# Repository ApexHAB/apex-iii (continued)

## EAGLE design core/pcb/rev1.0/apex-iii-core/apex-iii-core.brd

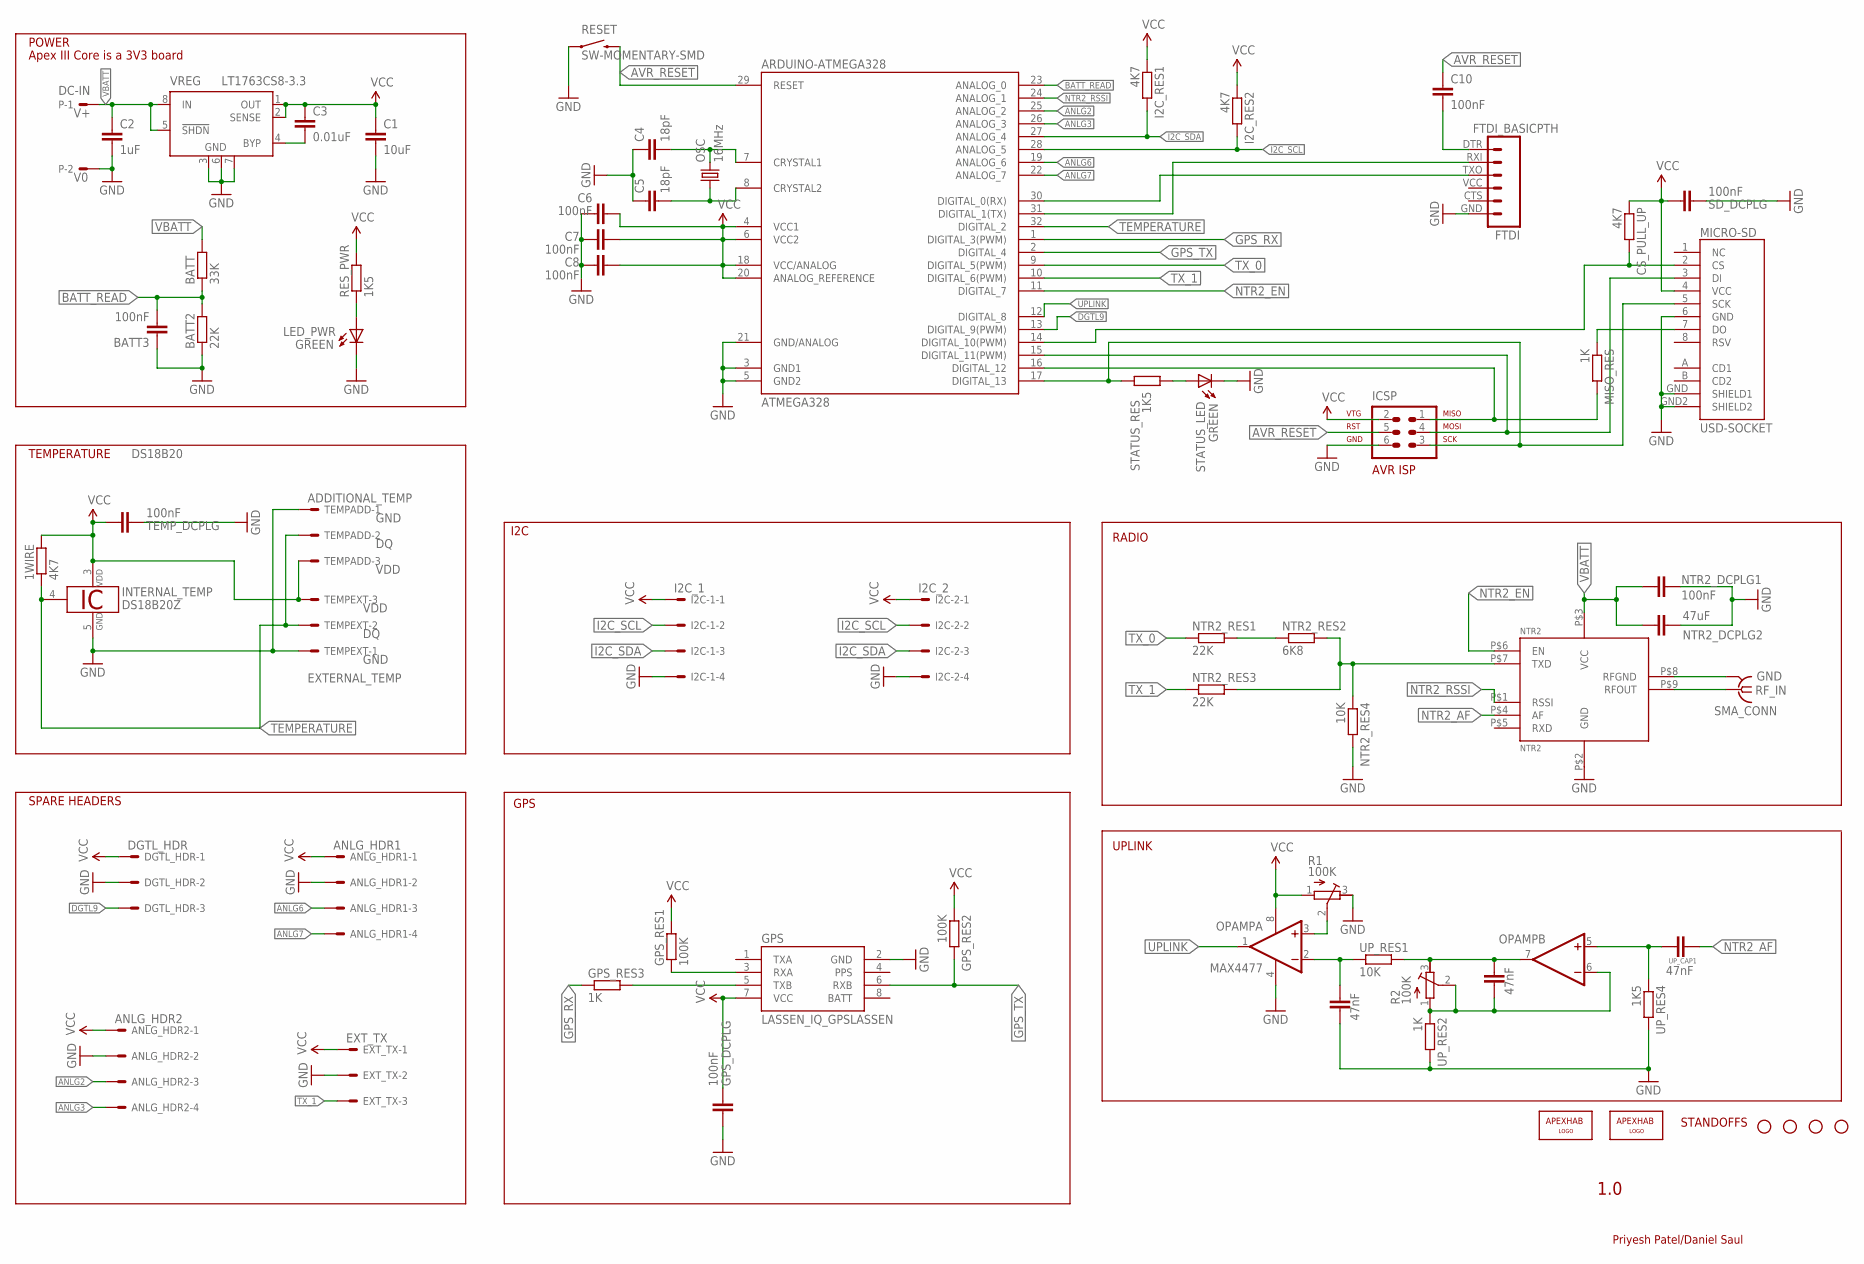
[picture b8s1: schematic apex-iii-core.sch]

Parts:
1WIRE: 4K7; R0805
ANLG_HDR1: ANLG_HDR1; 6410-04
ANLG_HDR2: ANLG_HDR2; 6410-04
ARDUINO-ATMEGA328: ATMEGA328; TQFP32-08
BATT: 33K; R0805
BATT2: 22K; R0805
BATT3: 100nF; 0805
C1: 10uF; 0805
C2: 1uF; 0805
C3: 0.01uF; 0805
C4, C5: 18pF; 0805
C6, C7, C8, C10: 100nF; 0805
CS_PULL_UP: 4K7; R0805
DGTL_HDR: DGTL_HDR; 6410-03
EXT_TX: EXT_TX; 6410-03
FTDI: FTDI_BASICPTH; FTDI_BASIC
GPS: LASSEN_IQ_GPSLASSEN; LASSEN_IQ_GPS
GPS_DCPLG: 100nF; 0805
GPS_RES1, GPS_RES2: 100K; R0805
GPS_RES3: 1K; R0805
I2C-1: I2C_1; 6410-04
I2C-2: I2C_2; 6410-04
I2C_RES1, I2C_RES2: 4K7; R0805
ICSP: AVR-ISP-6
INTERNAL_TEMP: DS18B20Z; SO08
JP1, JP2, JP3, JP4: STAND-OFF
JP5: APEXHAB-LOGO_APEXHAB-SMALL; APEXHAB-LOGO-SMALL
JP6: APEXHAB-LOGO_APEXHAB; APEXHAB-LOGO
LED_PWR: GREEN; CHIPLED_0603
MICRO-SD: USD-SOCKET; MICRO-SD-PUSH-PULL
MISO_RES: 1K; R0805
NTR2: NTR2
NTR2_DCPLG1: 100nF; 0805
NTR2_DCPLG2: 47uF; 0805
NTR2_RES1, NTR2_RES3: 22K; R0805
NTR2_RES2: 6K8; R0805
NTR2_RES4: 10K; R0805
OPAMP: MAX4477; SO08
OSC: 16MHz; CRYSTAL-SMD-5X3
P: DC-IN; 6410-02
R1, R2: 100K; RTRIM3214W
RESET: SW-MOMENTARY-SMD; TACTILE-SWITCH-1101NE
RES_PWR: 1K5; R0805
SD_DCPLG: 100nF; 0805
SMA_CONN: SMA-142-0701-801/806; J502-ND-142-0701-801/806
STATUS_LED: GREEN; CHIPLED_0603
STATUS_RES: 1K5; R0805
TEMPADD: ADDITIONAL_TEMP; 6410-03
TEMPEXT: EXTERNAL_TEMP; 6410-03
TEMP_DCPLG: 100nF; 0805
UP_CAP1, UP_CAP3, UP_CAP4: 47nF; 0805
UP_RES1: 10K; R0805
UP_RES2: 1K; R0805
UP_RES4: 1K5; R0805
VREG: LT1763CS8-3.3; SOIC8

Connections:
ANLG2: ANLG_HDR2.3, ARDUINO-ATMEGA328.25 (ANALOG_2)
ANLG3: ANLG_HDR2.4, ARDUINO-ATMEGA328.26 (ANALOG_3)
ANLG6: ANLG_HDR1.3, ARDUINO-ATMEGA328.19 (ANALOG_6)
ANLG7: ANLG_HDR1.4, ARDUINO-ATMEGA328.22 (ANALOG_7)
AVR_RESET: ARDUINO-ATMEGA328.29 (RESET), C10.1, ICSP.5, RESET.P$2 (2)
BATT: GPS.8 (BATT)
BATT_READ: ARDUINO-ATMEGA328.23 (ANALOG_0), BATT.1, BATT2.2, BATT3.2
DGTL9: ARDUINO-ATMEGA328.13 (DIGITAL_9(PWM)), DGTL_HDR.3
GND: ANLG_HDR1.2, ANLG_HDR2.2, ARDUINO-ATMEGA328.3 (GND1), ARDUINO-ATMEGA328.5 (GND2), ARDUINO-ATMEGA328.21 (GND/ANALOG), BATT2.1, BATT3.1, C1.2, C2.2, C4.1, C5.1, C6.1, C7.1, C8.1, DGTL_HDR.2, EXT_TX.2, FTDI.GND (6), GPS.2 (GND), GPS_DCPLG.2, I2C-1.4, I2C-2.4, ICSP.6, INTERNAL_TEMP.5 (GND), LED_PWR.C, MICRO-SD.6 (GND), MICRO-SD.GND (SHIELD1), MICRO-SD.GND2 (SHIELD2), NTR2.P$2 (GND), NTR2.P$8 (RFGND), NTR2_DCPLG1.1, NTR2_DCPLG2.1, NTR2_RES4.2, OPAMP.4 (V-), P.2, R1.3 (A), RESET.P$1 (1), SD_DCPLG.1, SMA_CONN.G@1 (GND), SMA_CONN.G@2 (GND), SMA_CONN.G@3 (GND), SMA_CONN.G@4 (GND), STATUS_LED.C, TEMPADD.1, TEMPEXT.1, TEMP_DCPLG.1, UP_CAP4.2, UP_RES2.2, UP_RES4.2, VREG.3 (GND), VREG.6 (GND), VREG.7 (GND)
GPS_RX: ARDUINO-ATMEGA328.1 (DIGITAL_3(PWM)), GPS_RES3.1
GPS_TX: ARDUINO-ATMEGA328.2 (DIGITAL_4), GPS.6 (RXB), GPS_RES2.2
I2C_SCL: ARDUINO-ATMEGA328.28 (ANALOG_5), I2C-1.2, I2C-2.2, I2C_RES2.2
I2C_SDA: ARDUINO-ATMEGA328.27 (ANALOG_4), I2C-1.3, I2C-2.3, I2C_RES1.2
MISO: ARDUINO-ATMEGA328.16 (DIGITAL_12), ICSP.1, MISO_RES.2
MOSI: ARDUINO-ATMEGA328.15 (DIGITAL_11(PWM)), ICSP.4, MICRO-SD.3 (DI)
unnamed: C3.2, VREG.4 (BYP)
unnamed: MICRO-SD.7 (DO), MISO_RES.1
unnamed: LED_PWR.A, RES_PWR.1
unnamed: C10.2, FTDI.DTR (1)
unnamed: ARDUINO-ATMEGA328.8 (CRYSTAL2), C5.2, OSC.1
unnamed: ARDUINO-ATMEGA328.7 (CRYSTAL1), C4.2, OSC.3 (2)
unnamed: STATUS_LED.A, STATUS_RES.2
unnamed: ARDUINO-ATMEGA328.31 (DIGITAL_1(TX)), FTDI.RXI (2)
unnamed: ARDUINO-ATMEGA328.30 (DIGITAL_0(RX)), FTDI.TXO (3)
unnamed: ARDUINO-ATMEGA328.14 (DIGITAL_10(PWM)), CS_PULL_UP.2, MICRO-SD.2 (CS)
unnamed: NTR2.P$7 (TXD), NTR2_RES2.2, NTR2_RES3.2, NTR2_RES4.1
unnamed: GPS.3 (RXA), GPS_RES1.1
unnamed: GPS.5 (TXB), GPS_RES3.2
unnamed: OPAMP.3 (+IN), R1.2 (S)
unnamed: NTR2_RES1.2, NTR2_RES2.1
unnamed: OPAMP.5 (+IN), UP_CAP1.2, UP_RES4.1
unnamed: OPAMP.7 (OUT), R2.3 (A), UP_CAP3.1, UP_RES1.2
unnamed: OPAMP.6 (-IN), R2.1 (E), R2.2 (S), UP_CAP3.2, UP_RES2.1
NTR2_AF: NTR2.P$4 (AF), UP_CAP1.1
NTR2_EN: ARDUINO-ATMEGA328.11 (DIGITAL_7), NTR2.P$6 (EN)
NTR2_RSSI: ARDUINO-ATMEGA328.24 (ANALOG_1), NTR2.P$1 (RSSI)
RANDOM: OPAMP.2 (-IN), UP_CAP4.1, UP_RES1.1
RF_IN: NTR2.P$9 (RFOUT), SMA_CONN.1
SCK: ARDUINO-ATMEGA328.17 (DIGITAL_13), ICSP.3, MICRO-SD.5 (SCK), STATUS_RES.1
TEMPERATURE: 1WIRE.1, ARDUINO-ATMEGA328.32 (DIGITAL_2), INTERNAL_TEMP.4 (1W), TEMPADD.2, TEMPEXT.2
TX_0: ARDUINO-ATMEGA328.9 (DIGITAL_5(PWM)), NTR2_RES1.1
TX_1: ARDUINO-ATMEGA328.10 (DIGITAL_6(PWM)), EXT_TX.3, NTR2_RES3.1
UPLINK: ARDUINO-ATMEGA328.12 (DIGITAL_8), OPAMP.1 (OUT)
VBATT: BATT.2, C2.1, NTR2.P$3 (VCC), NTR2_DCPLG1.2, NTR2_DCPLG2.2, P.1, VREG.5 (!SHDN), VREG.8 (IN)
VCC: 1WIRE.2, ANLG_HDR1.1, ANLG_HDR2.1, ARDUINO-ATMEGA328.4 (VCC1), ARDUINO-ATMEGA328.6 (VCC2), ARDUINO-ATMEGA328.18 (VCC/ANALOG), ARDUINO-ATMEGA328.20 (ANALOG_REFERENCE), C1.1, C3.1, C6.2, C7.2, C8.2, CS_PULL_UP.1, DGTL_HDR.1, EXT_TX.1, GPS.7 (VCC), GPS_DCPLG.1, GPS_RES1.2, GPS_RES2.1, I2C-1.1, I2C-2.1, I2C_RES1.1, I2C_RES2.1, ICSP.2, INTERNAL_TEMP.3 (VDD), MICRO-SD.4 (VCC), OPAMP.8 (V+), R1.1 (E), RES_PWR.2, SD_DCPLG.2, TEMPADD.3, TEMPEXT.3, TEMP_DCPLG.2, VREG.1 (OUT), VREG.2 (SENSE)

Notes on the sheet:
POWER
1.0
Priyesh Patel/Daniel Saul
TEMPERATURE
GND
VDD
DS18B20
Apex III Core is a 3V3 board
RADIO
GPS
SPARE HEADERS
STANDOFFS
I2C
UPLINK

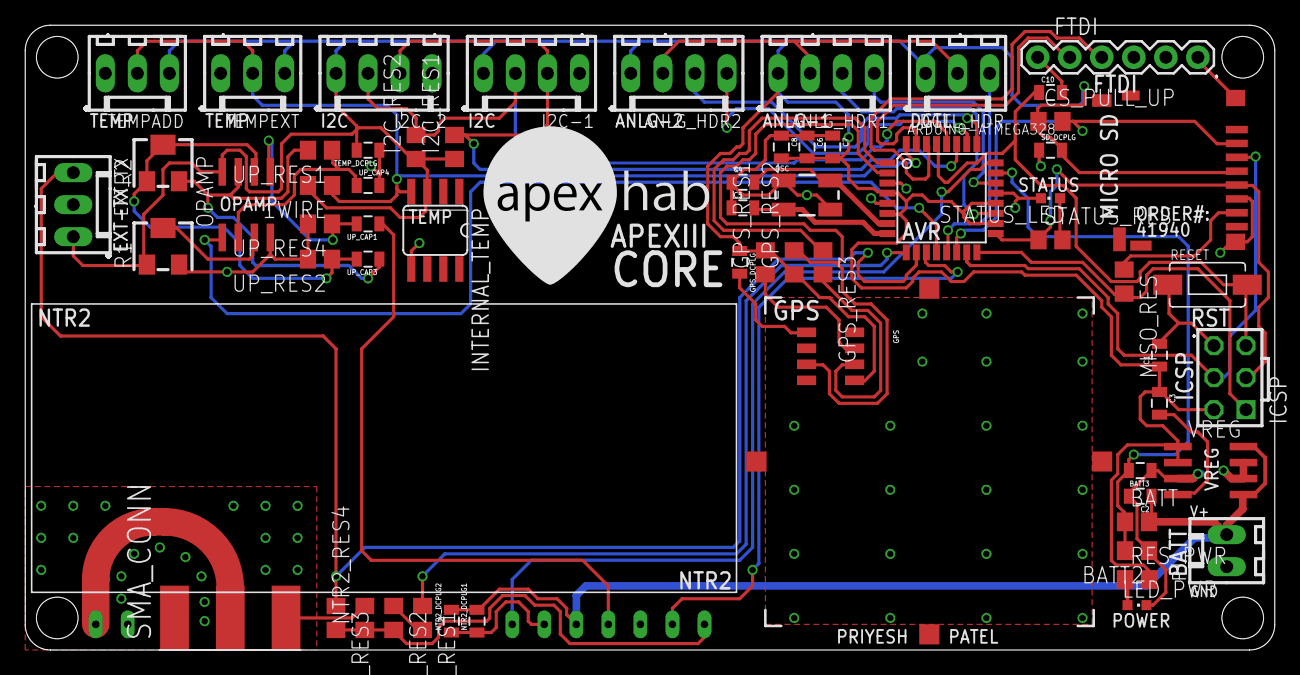
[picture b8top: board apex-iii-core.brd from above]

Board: 2 copper layers, 99.1 x 49.5 mm, 68 parts (1 on the bottom side), 44 nets.

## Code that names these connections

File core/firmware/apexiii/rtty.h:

/**
 * rtty.h
 *
 * Part of the Apex III project
 * http://www.apexhab.org/apex-iii/
 *
 * Priyesh Patel
 *
 * (c) Copyright ApexHAB 2011
 * team@apexhab.org
 */

/*
 * Bauds:
 *  default = 50 baud
 *  0 = 50 baud
 *  1 = 300 baud
 */

#ifndef RTTY_H
#define RTTY_H

#include "Arduino.h"
#include "util/crc16.h"

#define TX_0 5
#define TX_1 6
#define NTR2_EN 7

void rtty_init();
void rtty_prepare(char* sentence);
void rtty_tx(char* sentence, int baud);
void rtty_preamble(int baud);
void rtty_tx_byte(char c, int baud);
void rtty_tx_bit(int b, int baud);
uint16_t rtty_crc16_ccitt_checksum(char* sentence);

#endif

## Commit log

2011-11-09 added readme
2011-11-09 created directory structure
2011-12-09 progress with apex iii core sch
2011-12-29 new .gitignore
2011-12-29 slight changes to schematic
2011-12-31 final core schematic
2011-12-31 i2c resistors
2011-12-31 ntr2 DS
2011-12-31 end of day commit - board very messy
2012-01-02 core pcb
2012-01-03 continued with PCB + readme
2012-01-04 pcb mainly finished
2012-01-04 Core pcb finished
2012-01-05 core pcb sent to fab house
2012-01-07 ported over alpha firmware - still requires work to function
2012-01-14 setup module folders
2012-01-14 finished siren
2012-01-14 siren pngs exported
2012-01-14 added cutdown to siren
2012-01-15 pressure + himidity boards
2012-01-15 rename
2012-01-15 siren pcb
2012-01-15 Added ADC, Radiation and tilt control module schematics & PCBs
2012-01-15 fix airwires, rename, export larger pngs
2012-01-15 Finished light sensor module
2012-01-15 light module finished
2012-01-18 module gerbers sent off
2012-02-03 core firmware
2012-02-11 upgraded core firmware to arduino 1.0
2012-02-11 clean up + added ground speed
2012-02-11 module comms
2012-02-12 more work on firmware
2012-02-15 escape while loops when module is dead
2012-02-16 ext temp sensor address
2012-02-18 improving core firmware and module framework
2012-02-18 cleaning up GPS code
2012-02-19 completely rewrote GPS code, tidied up rest of the firmware too
2012-02-19 finished cutdown + siren firmware
2012-02-19 module framework added
2012-02-19 fixed tabs
2012-02-19 updated module framework
2012-02-19 module comms ready and tested
2012-02-19 Started tilt control firmare: no idea if it will work or not
2012-02-21 Tilt control firmware finished, pending check of PWM values
2012-02-21 Started ADC lemon firmware
2012-02-21 new module addresses
2012-02-21 Radiation firmware complete - ish - hopefully - maybe
2012-02-21 Added radiation b with a different address because Ill forget otherwise
2012-02-21 tidied up
2012-02-22 added pressure firmware and tidied up
2012-02-22 added pressure code to core
2012-02-24 bug fix by casting char
2012-02-25 Fixed tilt control syntax error
2012-02-25 allows light module to send back 8 bytes
2012-02-25 fixed bug on light firmware
2012-02-25 Light sensor firmware finished
2012-02-26 Core: changed callsign, changed sentence terminator, removed pressure for now
2012-02-28 progress from school
2012-02-29 Tilt is working
2012-02-29 changed packet structure
2012-02-29 final cleaned up core firmware
2012-03-01 launch 1 data
2012-03-01 renaming files
2012-03-01 Revert "renaming files"
    This reverts commit 3f0b59097893a2c4e10eab6c0de2b54217862d8e.
2012-03-01 changing file extensions
2012-03-01 added spacenearus screengrabs
2012-03-11 core transmits last known gps data rather than ,,,,, - ready for L2
2012-03-11 launch 2 data, tracks, logs from Core, GPX
2012-03-18 core firmware cleaned up
2012-04-27 north sea data added
2012-04-27 cleaned up kml
2013-03-24 light firmware for core board and updated libraries
2013-03-25 removed temp files
2013-03-29 changed preamble
